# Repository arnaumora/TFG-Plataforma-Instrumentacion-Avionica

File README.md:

# Real-Time Flight Instrumentation Platform (AHRS + PFD)

An ESP32-S3 sensor unit, built on a custom KiCad-designed PCB, estimates aircraft
attitude, heading, altitude and vertical speed in real time and streams them over a
2.4 GHz RF link to a Primary Flight Display (PFD) that renders a Basic-T instrument
layout with a moving map.

Bachelor's thesis (TFG), Aerospace Vehicle Engineering, UPC - ESEIAAT.

## Key results

- End-to-end latency (sensor to display) under 200 ms
- Display refresh rate above 60 FPS
- Total hardware cost under 100 EUR (custom PCB plus off-the-shelf sensors)
- Fully open-source: custom hardware and firmware

## Overview

The platform reproduces the core instruments of a glass cockpit on low-cost, custom
hardware. It has two parts communicating over a 2.4 GHz RF link:

- **Sensor unit (ESP32-S3, custom PCB):** reads the IMU and barometric sensor, runs a
  Mahony filter to estimate attitude (pitch and roll) and heading, derives altitude and
  vertical speed from atmospheric pressure, and transmits the state over the RF link.
- **Primary Flight Display (Processing):** receives the telemetry and renders a Basic-T
  layout together with a moving map in real time (attitude indicator, airspeed and altitude
  tapes, heading, map), following aeronautical display references (ARINC 429). The display
  can also be bridged to an Android device.

## Repository structure

```
Software/      ESP32-S3 firmware (C/C++), the PFD (Processing) and Python tooling
PCB/           custom PCB, designed in KiCad (schematic and layout)
LATEX/         thesis document (memoria) source
Presentacio/   defense presentation
Entrega/       final submission package
```

## Hardware

| Component         | Part                        |
|-------------------|-----------------------------|
| MCU               | ESP32-S3                    |
| PCB               | Custom, designed in KiCad   |
| IMU               | MPU-9250 (9-DOF)            |
| Barometric sensor | BMP280                      |
| RF transceiver    | NRF24L01+ (2.4 GHz)         |

Total bill of materials: under 100 EUR.

## Software and tech stack

- **Firmware:** C/C++ on the ESP32-S3 (I2C/SPI for the sensors, SPI for the RF module)
- **PFD:** Processing (Basic-T instruments and moving map)
- **Python tooling:** downloads the map tiles used by the PFD map, and bridges the
  connection to an Android device

## How it works

Attitude and heading are obtained by fusing the MPU-9250 accelerometer, gyroscope and
magnetometer with a Mahony filter. Altitude and vertical speed are derived from BMP280
barometric pressure. The sensor unit packs the state into a fixed-size telemetry packet
sent over the NRF24L01+ link, and the Processing PFD updates its render loop on each
packet, redrawing the Basic-T instruments and the moving map. Map tiles are fetched with
a Python script, and a second Python script handles the bridge to Android. Layout and
behavior reference ARINC 429 and standard PFD conventions.

## Build and run

```bash
git clone https://github.com/arnaumora/TFG-Plataforma-Instrumentacion-Avionica.git
```

- **Firmware (sensor unit):** open the ESP32-S3 firmware in `Software/` and flash it to the board.
- **PFD:** open the Processing sketch in `Software/` and run it (connect the RF receiver first).
- **Map tiles / Android:** run the Python scripts in `Software/` as needed.

## References

- ARINC 429
- [any papers or references on AHRS / sensor fusion you used]

## License

Released under the MIT License. See [LICENSE](LICENSE).

## Author

**Arnau Mora Pérez** - Aerospace Vehicle Engineering, UPC - ESEIAAT
[linkedin.com/in/arnau-mora](https://www.linkedin.com/in/arnau-mora)

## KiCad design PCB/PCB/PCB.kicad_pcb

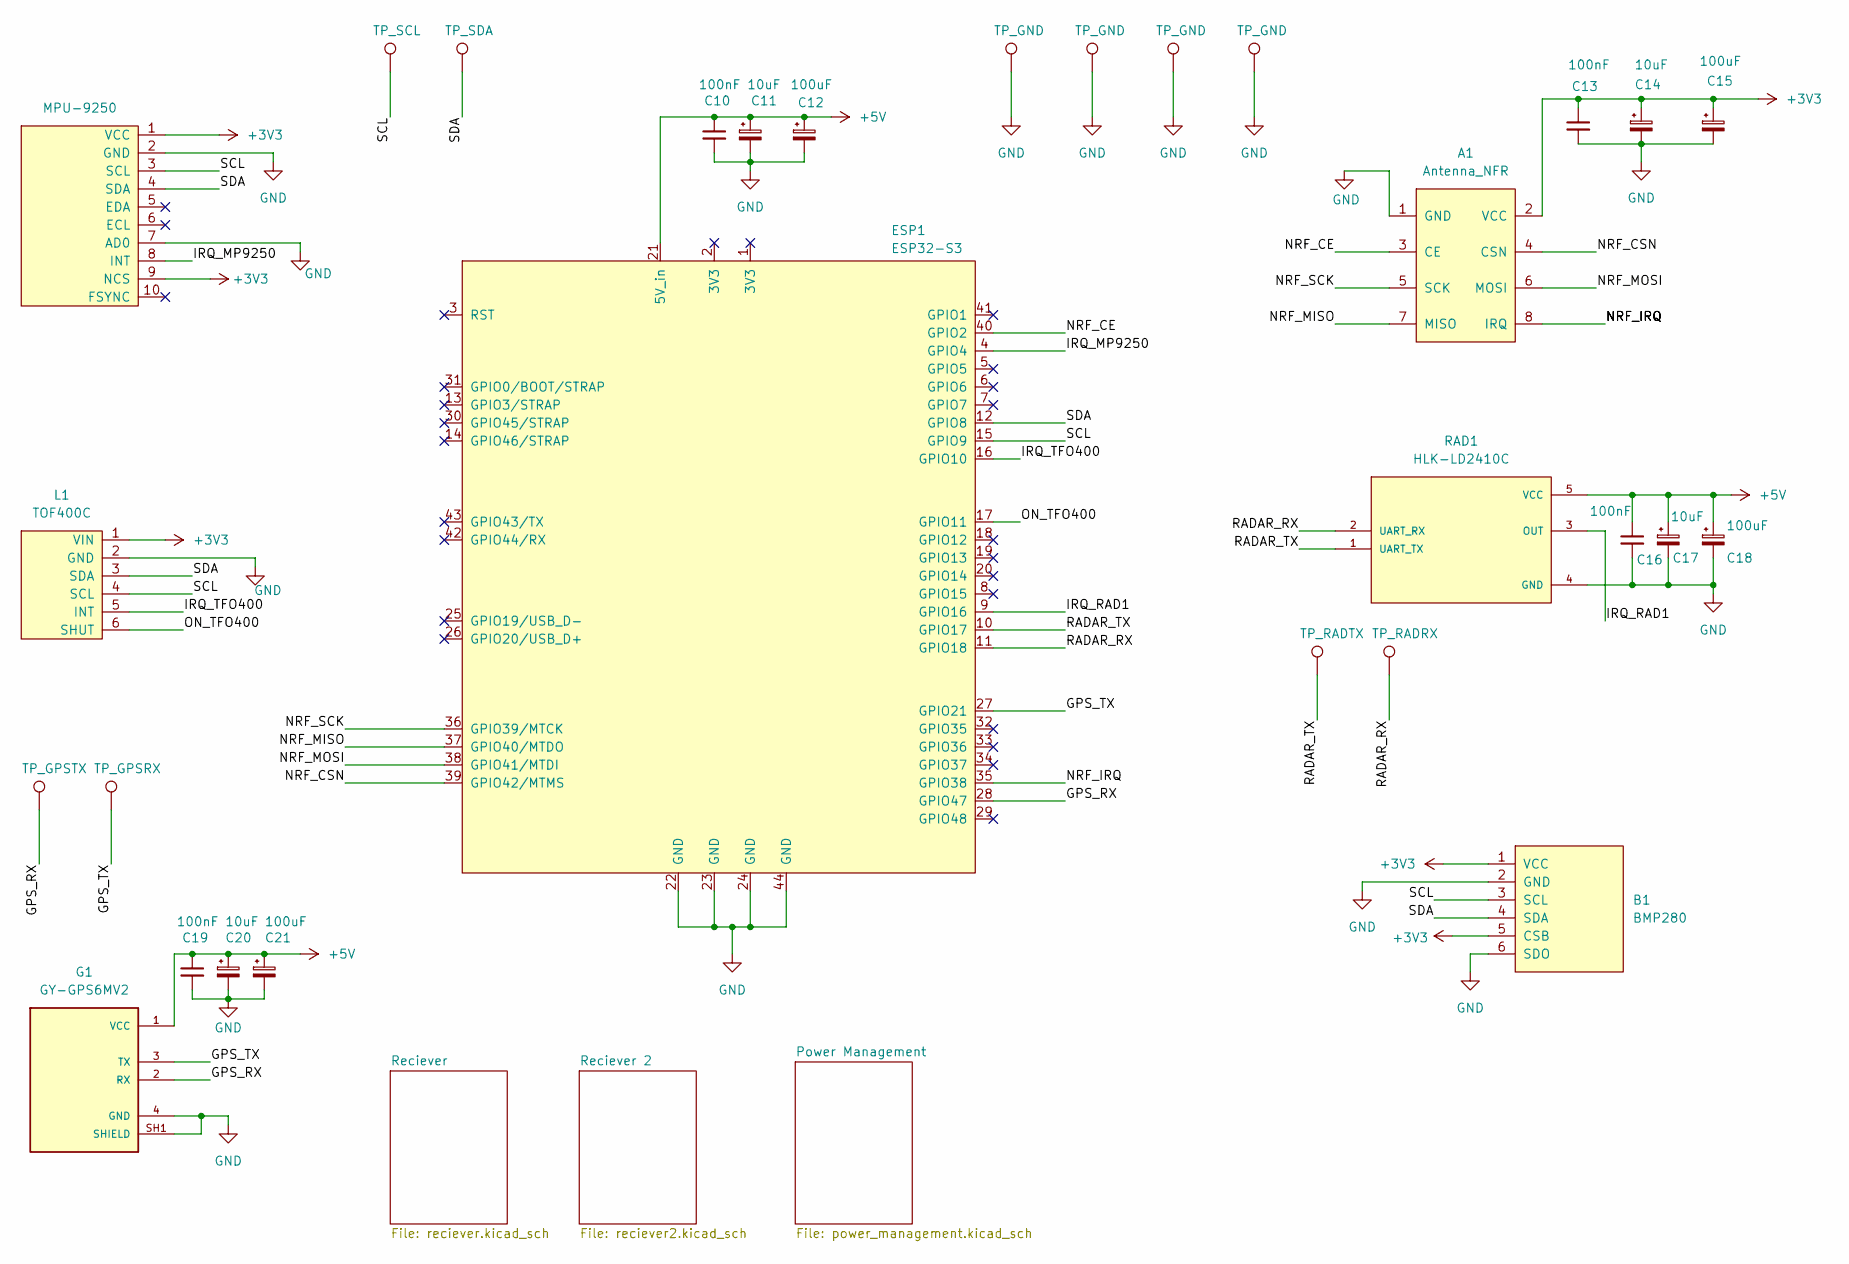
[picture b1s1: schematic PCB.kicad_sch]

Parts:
A1: Antenna_NFR; NFR24L01_TX
B1: BMP280
C10, C13, C16, C19: 100nF; C_1206_3216Metric_Pad1.33x1.80mm_HandSolder
C11, C14, C17, C20: 10uF; CP_EIA-6032-28_Kemet-C_HandSolder
C12, C15, C18, C21: 100uF; CP_EIA-7343-31_Kemet-D_HandSolder
ESP1: ESP32-S3; YD-ESP32
G1: GY-GPS6MV2
I1: MPU-9250
L1: TOF400C
RAD1: HLK-LD2410C
TP8, TP9, TP10, TP11: TP_GND; TestPoint_THTPad_D1.5mm_Drill0.7mm
TP12: TP_RADTX; TestPoint_THTPad_D1.5mm_Drill0.7mm
TP13: TP_RADRX; TestPoint_THTPad_D1.5mm_Drill0.7mm
TP14: TP_GPSRX; TestPoint_THTPad_D1.5mm_Drill0.7mm
TP15: TP_GPSTX; TestPoint_THTPad_D1.5mm_Drill0.7mm
TP16: TP_SCL; TestPoint_THTPad_D1.5mm_Drill0.7mm
TP17: TP_SDA; TestPoint_THTPad_D1.5mm_Drill0.7mm

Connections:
+3V3: A1.2 (VCC), B1.1 (VCC), B1.5 (CSB), C13.1, C14.1, C15.1, I1.1 (VCC), I1.9 (NCS), L1.1 (VIN); also elsewhere on the board
+5V: C10.1, C11.1, C12.1, C16.1, C17.1, C18.1, C19.1, C20.1, C21.1, ESP1.21 (5V_in), G1.1 (VCC), RAD1.5 (VCC); also elsewhere on the board
/GPS_RX: ESP1.28 (GPIO47), G1.2 (RX), TP15.1
/GPS_TX: ESP1.27 (GPIO21), G1.3 (TX), TP14.1
/IRQ_MP9250: ESP1.4 (GPIO4), I1.8 (INT)
/IRQ_RAD1: ESP1.9 (GPIO16), RAD1.3 (OUT)
/IRQ_TFO400: ESP1.16 (GPIO10), L1.5 (INT)
/NRF_CE: A1.3 (CE), ESP1.40 (GPIO2)
/NRF_CSN: A1.4 (CSN), ESP1.39 (GPIO42/MTMS)
/NRF_IRQ: A1.8 (IRQ), ESP1.35 (GPIO38)
/NRF_MISO: A1.7 (MISO), ESP1.37 (GPIO40/MTDO)
/NRF_MOSI: A1.6 (MOSI), ESP1.38 (GPIO41/MTDI)
/NRF_SCK: A1.5 (SCK), ESP1.36 (GPIO39/MTCK)
/ON_TFO400: ESP1.17 (GPIO11), L1.6 (SHUT)
/RADAR_RX: ESP1.11 (GPIO18), RAD1.2 (UART_RX), TP13.1
/RADAR_TX: ESP1.10 (GPIO17), RAD1.1 (UART_TX), TP12.1
/SCL: B1.3 (SCL), ESP1.15 (GPIO9), I1.3 (SCL), L1.4 (SCL), TP16.1
/SDA: B1.4 (SDA), ESP1.12 (GPIO8), I1.4 (SDA), L1.3 (SDA), TP17.1
GND: A1.1 (GND), B1.2 (GND), B1.6 (SDO), C10.2, C11.2, C12.2, C13.2, C14.2, C15.2, C16.2, C17.2, C18.2, C19.2, C20.2, C21.2, ESP1.22 (GND), ESP1.23 (GND), ESP1.24 (GND), ESP1.44 (GND), G1.4 (GND), G1.SH1 (SHIELD), I1.2 (GND), I1.7 (AD0), L1.2 (GND), RAD1.4 (GND), TP8.1, TP9.1, TP10.1, TP11.1; also elsewhere on the board

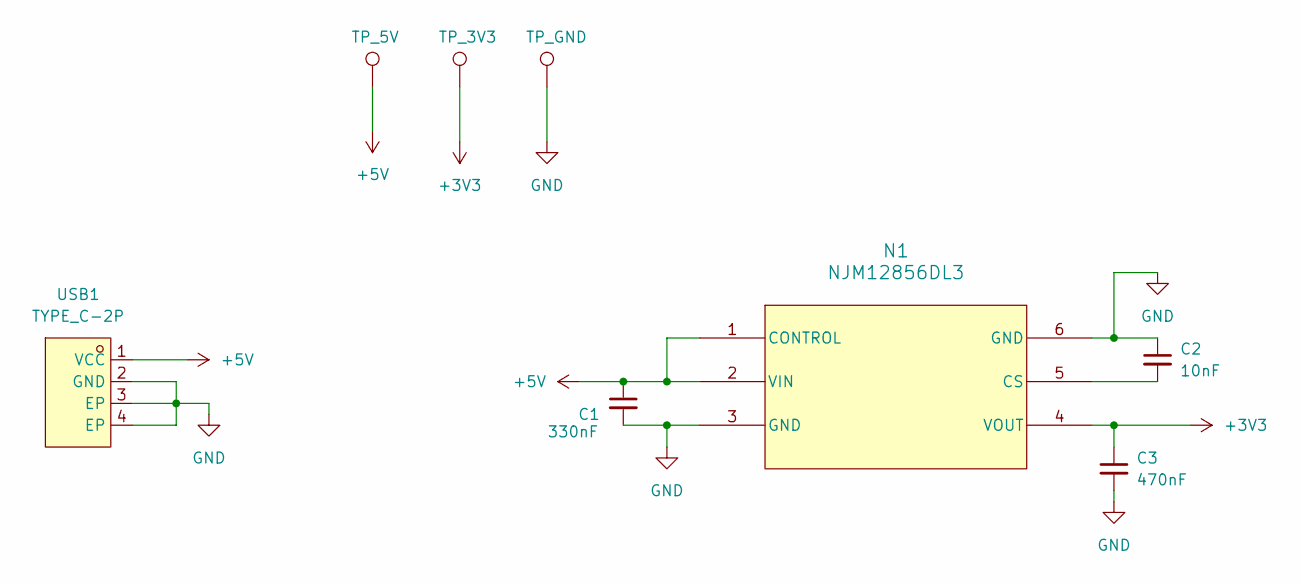
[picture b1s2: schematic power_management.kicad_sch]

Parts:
C1: 330nF; C_1206_3216Metric_Pad1.33x1.80mm_HandSolder
C2: 10nF; C_1206_3216Metric_Pad1.33x1.80mm_HandSolder
C3: 470nF; C_1812_4532Metric_Pad1.57x3.40mm_HandSolder
N1: NJM12856DL3
TP1: TP_5V; TestPoint_Pad_2.0x2.0mm
TP2: TP_3V3; TestPoint_Pad_2.0x2.0mm
TP3: TP_GND; TestPoint_Pad_2.0x2.0mm
USB1: TYPE_C-2P

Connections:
+3V3: C3.1, N1.4 (VOUT), TP2.1; also elsewhere on the board
+5V: C1.1, N1.1 (CONTROL), N1.2 (VIN), TP1.1, USB1.1 (VCC); also elsewhere on the board
GND: C1.2, C2.1, C3.2, N1.3 (GND), N1.6 (GND), TP3.1, USB1.2 (GND), USB1.3 (EP), USB1.4 (EP); also elsewhere on the board
unnamed: C2.2, N1.5 (CS)

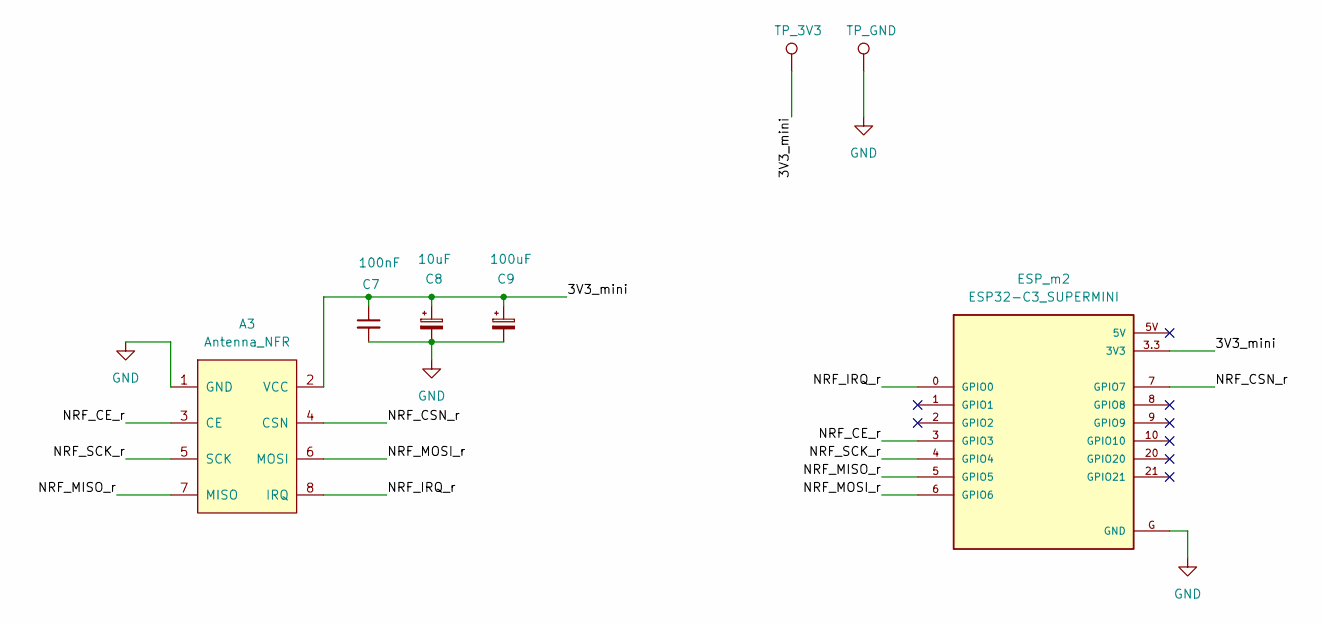
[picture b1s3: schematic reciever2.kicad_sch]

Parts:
A3: Antenna_NFR; NFR24L01_RX
C7: 100nF; C_1206_3216Metric_Pad1.33x1.80mm_HandSolder
C8: 10uF; CP_EIA-7343-31_Kemet-D_HandSolder
C9: 100uF; CP_EIA-7343-31_Kemet-D_HandSolder
ESP_m2: ESP32-C3_SUPERMINI
TP4: TP_3V3; TestPoint_Pad_2.0x2.0mm
TP5: TP_GND; TestPoint_Pad_2.0x2.0mm

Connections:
/Reciever 2/3V3_mini: A3.2 (VCC), C7.1, C8.1, C9.1, ESP_m2.3.3 (3V3), TP4.1
/Reciever 2/NRF_CE_r: A3.3 (CE), ESP_m2.3 (GPIO3)
/Reciever 2/NRF_CSN_r: A3.4 (CSN), ESP_m2.7 (GPIO7)
/Reciever 2/NRF_IRQ_r: A3.8 (IRQ), ESP_m2.0 (GPIO0)
/Reciever 2/NRF_MISO_r: A3.7 (MISO), ESP_m2.5 (GPIO5)
/Reciever 2/NRF_MOSI_r: A3.6 (MOSI), ESP_m2.6 (GPIO6)
/Reciever 2/NRF_SCK_r: A3.5 (SCK), ESP_m2.4 (GPIO4)
GND: A3.1 (GND), C7.2, C8.2, C9.2, ESP_m2.G (GND), TP5.1; also elsewhere on the board

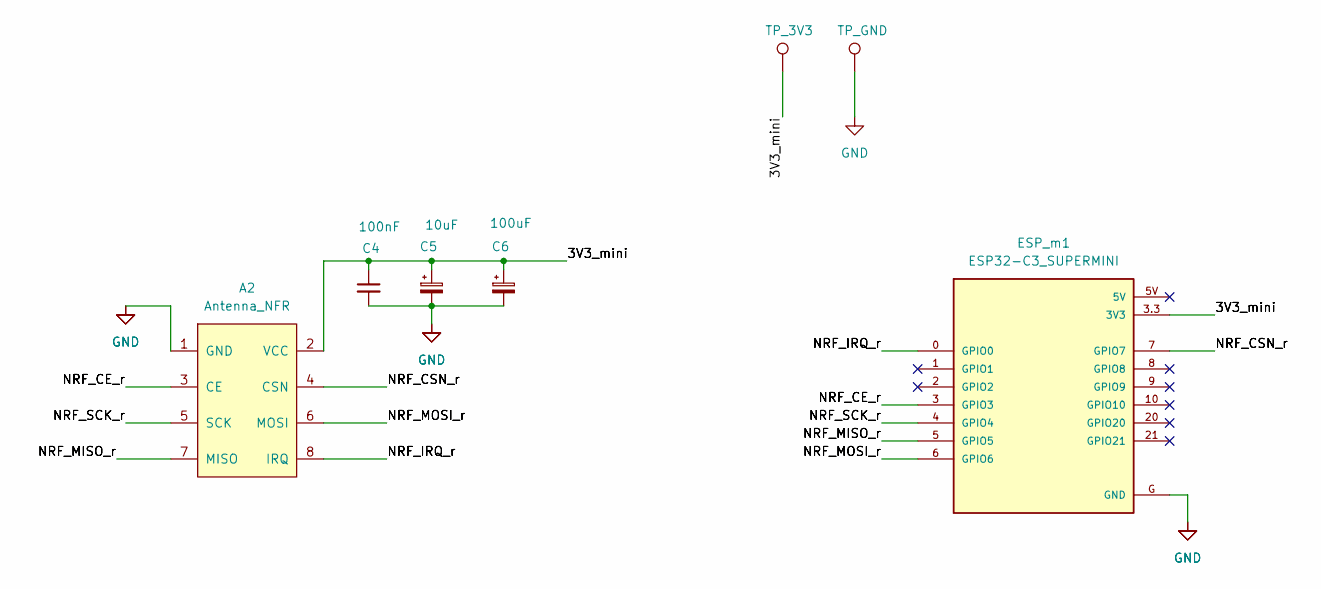
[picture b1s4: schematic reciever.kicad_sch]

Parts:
A2: Antenna_NFR; NFR24L01_RX
C4: 100nF; C_1206_3216Metric_Pad1.33x1.80mm_HandSolder
C5: 10uF; CP_EIA-7343-31_Kemet-D_HandSolder
C6: 100uF; CP_EIA-7343-31_Kemet-D_HandSolder
ESP_m1: ESP32-C3_SUPERMINI
TP6: TP_3V3; TestPoint_Pad_2.0x2.0mm
TP7: TP_GND; TestPoint_Pad_2.0x2.0mm

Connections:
/Reciever/3V3_mini: A2.2 (VCC), C4.1, C5.1, C6.1, ESP_m1.3.3 (3V3), TP6.1
/Reciever/NRF_CE_r: A2.3 (CE), ESP_m1.3 (GPIO3)
/Reciever/NRF_CSN_r: A2.4 (CSN), ESP_m1.7 (GPIO7)
/Reciever/NRF_IRQ_r: A2.8 (IRQ), ESP_m1.0 (GPIO0)
/Reciever/NRF_MISO_r: A2.7 (MISO), ESP_m1.5 (GPIO5)
/Reciever/NRF_MOSI_r: A2.6 (MOSI), ESP_m1.6 (GPIO6)
/Reciever/NRF_SCK_r: A2.5 (SCK), ESP_m1.4 (GPIO4)
GND: A2.1 (GND), C4.2, C5.2, C6.2, ESP_m1.G (GND), TP7.1; also elsewhere on the board

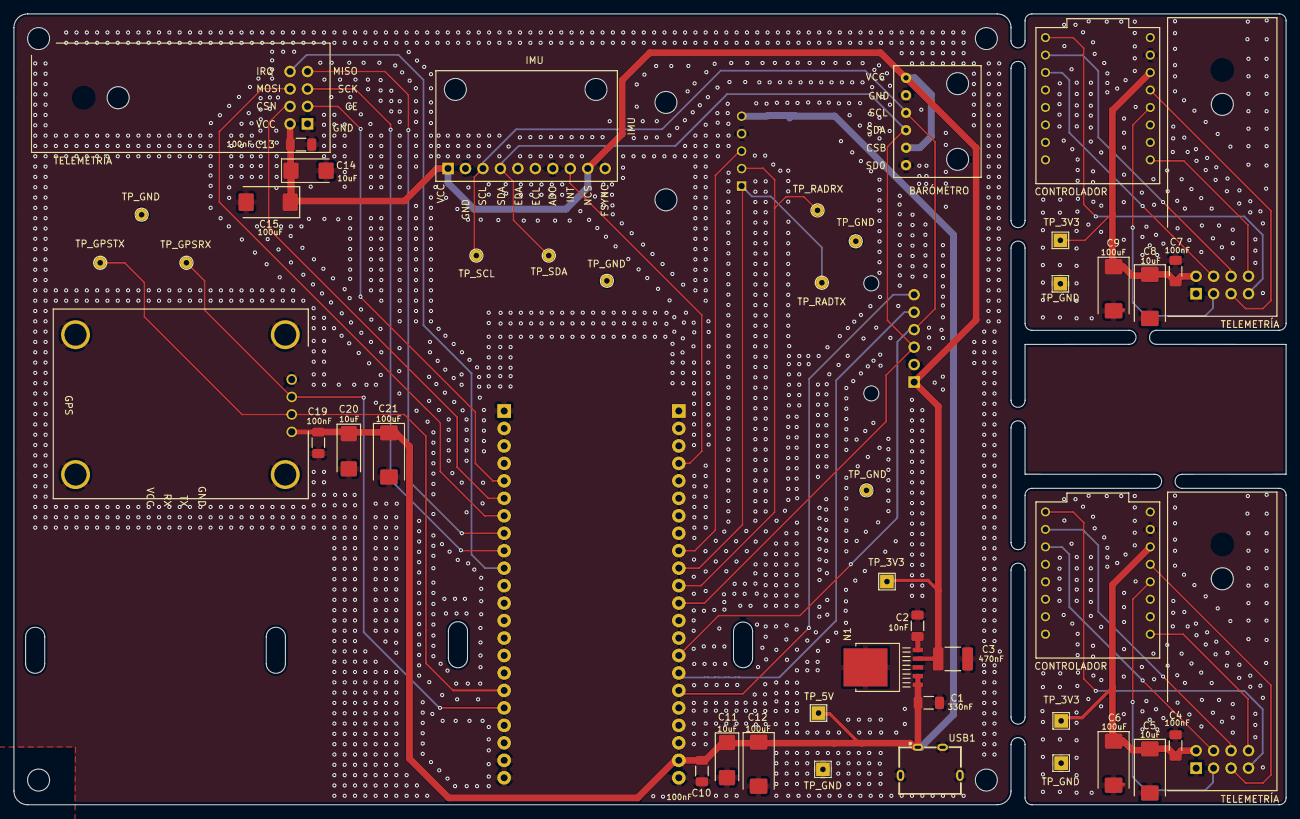
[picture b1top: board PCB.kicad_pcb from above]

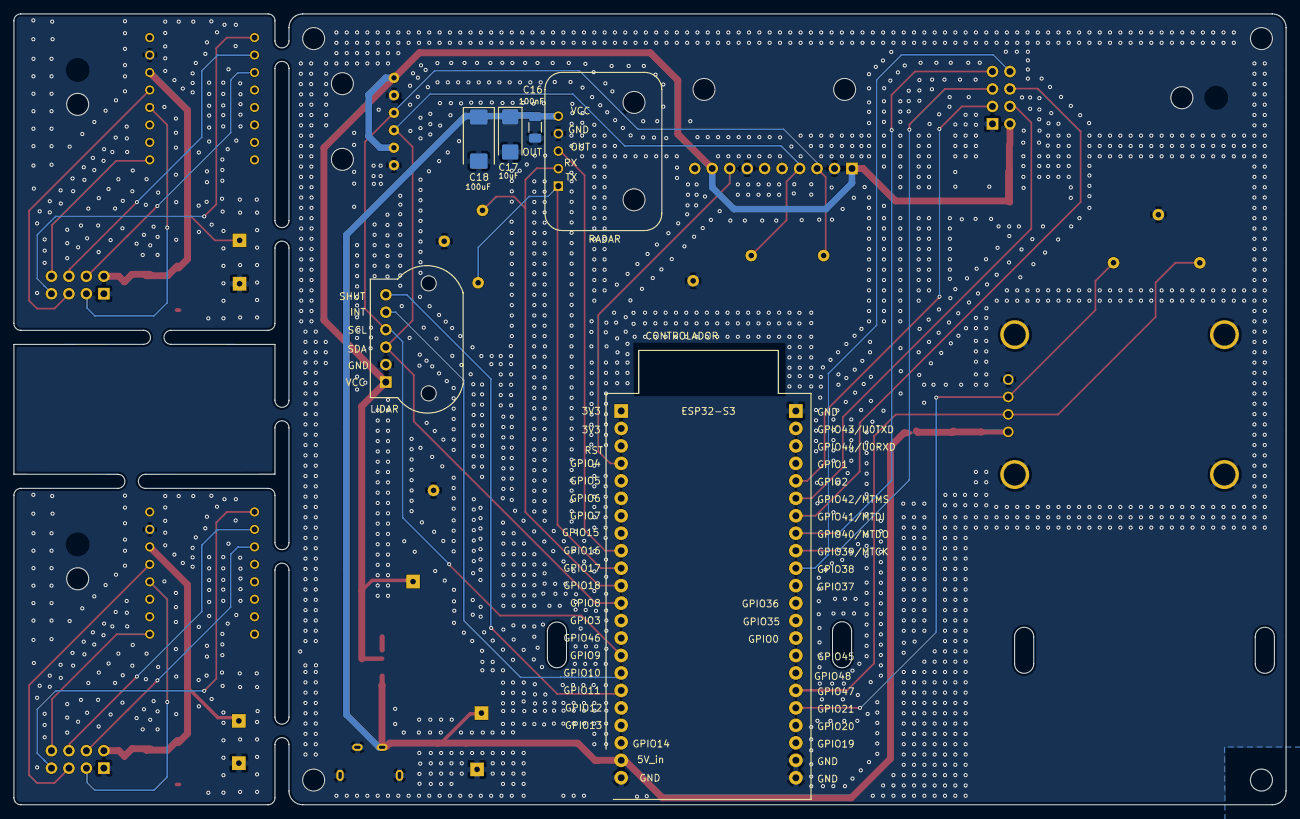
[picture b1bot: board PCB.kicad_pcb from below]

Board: 2 copper layers, 185.0 x 115.0 mm, 55 parts (6 on the bottom side), 34 nets.

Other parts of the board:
Agujero: -; Agujero
Agujero#2, Agujero#3, Agujero#4: -; Agujero

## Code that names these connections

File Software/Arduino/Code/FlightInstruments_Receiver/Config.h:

// Config.h - constantes de hardware y parametros de ajuste

#ifndef CONFIG_H
#define CONFIG_H

// DEBUG
// #define DEBUG_SERIAL

// MAG Calibration
// #define CALIBRATE_MAG 


// Definicion Pines

// I2C compartido (MPU-9250 + BMP280 + VL53L1X)
#define PIN_SDA        8
#define PIN_SCL        9

// LED RGB onboard
#define PIN_LED_RGB    48

// NRF24L01+PA+LNA (SPI)
#define NRF_SCK        39
#define NRF_MISO       40
#define NRF_MOSI       41
#define NRF_CE         2
#define NRF_CSN        42
#define NRF_IRQ        38

// GPS NEO-6M (UART1)
#define GPS_RX_PIN     21   // ESP32 RX <- GPS TX
#define GPS_TX_PIN     47   // ESP32 TX -> GPS RX
#define GPS_BAUD       9600

// HLK-LD2410C radar (UART2)
#define RADAR_RX_PIN   17
#define RADAR_TX_PIN   18
#define RADAR_BAUD     256000

// Interrupciones / control (no usadas en el codigo, pero asignadas)
#define TOF_SHUT_PIN   11   // XSHUT del TOF400C
#define TOF_IRQ_PIN    10   // INT del TOF400C
#define RADAR_IRQ_PIN  16
#define MPU_IRQ_PIN    4

// Direcciones I2C
#define MPU9250_ADDR   0x68   // AD0 a GND
#define AK8963_ADDR    0x0C   // magnetometro en el MPU-9250
#define BMP280_ADDR    0x76   // SDO a GND
#define VL53L1X_ADDR   0x29   // direccion por defecto del TOF400C
#define I2C_CLOCK      400000 // 400 kHz (Fast Mode)

// Rangos del MPU-9250
// Factores sacados del datasheet PS-MPU-9250A-01 Rev 1.1
#define ACCEL_SCALE    8192.0  // LSB/g     a +/-4g
#define GYRO_SCALE     65.5    // LSB/(deg/s) a +/-500deg/s
#define MAG_SCALE      0.15    // uT/LSB    en 16 bits

// BMP280
#define SEA_LEVEL_HPA      1013.25f   // presion de referencia ISA
#define VSPEED_ALPHA       0.2f      // suavizado EMA de la velocidad vertical

// VL53L1X / TOF400C
#define TOF_TIMING_BUDGET_US   50000   // 50 ms modo Long permite hasta 4 m
#define TOF_CONTINUOUS_MS      50      // 20 Hz
#define TOF_DEAD_ZONE_MM       40      // por debajo de aqui la medida no es fiable

// HLK-LD2410C

// Resolucion del gate.
#define RADAR_GATE_WIDTH_CM    20

// Thresholds por gate (downward-facing)
#define RADAR_SENS_GATE_0      80   // 0.00 - 0.20 m 
#define RADAR_SENS_GATE_1      70    // 0.20 - 0.40 m
#define RADAR_SENS_GATE_2      60    // 0.40 - 0.60 m
#define RADAR_SENS_GATE_3      50    // 0.60 - 0.80 m
#define RADAR_SENS_GATE_FAR    35    // 0.80 - 1.80 m  (gates 4-8)

// Peak-finder (modo enhanced)
#define RADAR_NOISE_FLOOR      40

// Suavizado EMA de la distancia derivada por gate
#define RADAR_DIST_ALPHA       0.40f

#define RADAR_HOVER_SPEED_KMH  2.0f  // por debajo de esta velocidad se considera hover
#define RADAR_ALERT_ENERGY_MIN 30    // energia minima para disparar alerta

// Zona de proximidad en funcion de la distancia
#define RADAR_ZONE_NONE        0
#define RADAR_ZONE_DANGER      1     // 0.00 - 0.60 m  (gates 0-2)
#define RADAR_ZONE_CAUTION     2     // 0.60 - 1.20 m  (gates 3-5)
#define RADAR_ZONE_CLEAR       3     // 1.20 - 1.80 m  (gates 6-8)

// Tasas de muestreo
#define SENSOR_RATE_HZ       100      // IMU + fusion
#define SENSOR_INTERVAL_US   (1000000 / SENSOR_RATE_HZ)

#define BARO_RATE_HZ         10
#define BARO_INTERVAL_MS     (1000 / BARO_RATE_HZ)

#define RADAR_PRINT_HZ       2
#define RADAR_PRINT_INTERVAL (1000 / RADAR_PRINT_HZ)

#define SERIAL_PRINT_HZ      10
#define SERIAL_PRINT_INTERVAL (1000 / SERIAL_PRINT_HZ)

// Calibracion del giroscopio
#define CALIBRATION_SAMPLES              500
#define CALIBRATION_VARIANCE_THRESHOLD   2.0

// Mahony
#define MAHONY_KP              3.0f
#define MAHONY_KI              1.0f


// CALIBRACION DEL MAGNETOMETRO (Hard iron / Soft iron)

// Hard iron offsets (uT) 
#define MAG_OFFSET_X    10.5555f
#define MAG_OFFSET_Y    -2.3537f
#define MAG_OFFSET_Z    -29.8582f

// Soft iron scales (adimensional)
#define MAG_SCALE_X     1.0277f
#define MAG_SCALE_Y     0.9899f
#define MAG_SCALE_Z     0.9849f

// CORRECCIONES DE HEADING
//
// Declinacion magnetica
// Diferencia entre el norte magnetico (lo que mide el sensor) y el
// norte geografico verdadero. Para obtener el valor real visitar la web
// (https://www.ncei.noaa.gov/products/world-magnetic-model)

#define MAG_DECLINATION_DEG    1.95f

// Offset entre el "forward" del IMU y el "forward" de la PCB
// Si la IMU esta rotada respecto a la placa, el heading
//  tendra un offset constante respecto al norte real.
// Tambien se puede usar para corregir errores constantes 
// que no provienen de la orientacion de la PCB

#define HEADING_BODY_OFFSET_DEG    0.0f

// Calibracion actitud 
#define PITCH_MOUNT_OFFSET_DEG    0.6f
#define ROLL_MOUNT_OFFSET_DEG     0.2f


// NRF24L01
#define NRF_CHANNEL            108
#define NRF_DATA_RATE          RF24_250KBPS
#define NRF_PA_LEVEL           RF24_PA_HIGH
#define NRF_RETRY_DELAY        5
#define NRF_RETRY_COUNT        15

#define NRF_ADDR_TX            "SENSR"
#define NRF_ADDR_RX            "CNTRL"

#define TELEMETRY_RATE_HZ      20
#define TELEMETRY_INTERVAL_MS  (1000 / TELEMETRY_RATE_HZ)

#endif
